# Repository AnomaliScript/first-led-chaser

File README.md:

# first-led-chaser
This project is meant to be an introduction to KiCad, as I have never fully, independently made a schematic before :(  Let's hope I can make this successfully!

## How to Use It
An LED Chaser is basically those glowing, flashy arcade signs that have a series of LEDs (not necessarily a series circuit, mind you) that light up in a particular order, whether it be every other LED that switches or the blinking LED follows a circular pattern.
It's purely for flashiness and style, and it looks cool!  For a project like mine, it can even show team spirit.  (Read more too see what team I'm making this LED Chaser for).

## Story and Why I Made This
First step of making the PCB is making the schematics.  In order to create a schematic, I used KiCad's schematic tool, and I placed a couple of components down, until I realized I needed to pull some components and their footprints (a footprint is what represents the component in the PCB editor) from a database called "Ultra Librarian" by Texas Instruments (they sponsor quite a lot of robotics teams).  After getting the needed schematics, I wired them together with the green copper lines, and learned how to use labels and global labels (global labels are the labels in the arrow shapes).

When switching over to the PCB editor for the second part of my project, I had to assign footprints to every one of the schematics: this is where Ultra Librarian helped me out in finding some footprints thatthe KiCad default library doesn't naturally have.

after hunting down all the footprints, I made the PCB board's shape.  This LED chaser I made is in the shape of my FRC Robotics Team's (1771) logo, and wiring it all together with the front and back coppers, with the help of vias, wasn't too daunting of a task the more I connected components.
It kinda felt like a game, connecting all of them together :)

Anyways, here's the final 3D result!

I'm debating on whether to make a case for it: I decided against it.

## BOM (my version)
0.01 uF Capacitors: [link](https://www.amazon.com/Cermant-Ceramic-Capacitor-Electronic-Components/dp/B09XV2CZJZ/ref=sr_1_3?sr=8-3)
1 uF Capacitors (and many more capacitors): [link](https://www.amazon.com/200PCS-Electrolytic-Capacitor-Kit-Electronics/dp/B0FH1R7N94/ref=sr_1_4?sr=8-4)
Connectors: [link](https://www.amazon.com/Glarks-Connector-Assortment-Stackable-Breakaway/dp/B07CWSXY7P)
4017BE: [link](https://www.amazon.com/Texas-Instruments-CD4017BE-Counter-Decoded/dp/B00GAGD10Y)
NE555N Clock: [link](https://www.amazon.com/ALLECIN-NE555-NE555P-Timer-NE555N/dp/B0CBKFMWDP)
T93YA: [link](https://www.digikey.com/en/products/detail/vishay-sfernice/T93YA103KT20/1587711)
In total, this project cost me about **$30** to make (yikes...)

## End Result
Fortunately, I got help from a friend when his dad agreed to lend me his solder and soldering iron.
When I initially soldered the PCB, [the blinking was really fast](https://drive.google.com/file/d/1CZGWTpNvm0oBers0KX6bNRDRQLqv2583/view?usp=sharing), even when I set the potentiometer to its "highest resistance" mode, which is stupposed to slow down the blinking rate.
After asking AI for help, I decided to replace the capacitor (which was originally 1uF) with a 10uF capacitor.

This solution worked, and after a few close burns, and the blinker works: a video of it blinking can be found [here](https://drive.google.com/file/d/13T7uWkx8QOqEzrhQr9J85-se3VObvKnz/view?usp=sharing) (the capacitor laying near the PCB was the 1uF capacitor that I removed).
Despite the blinker being a bit finicky at times, I learned a lot from this experience, and I'm still proud of the result.

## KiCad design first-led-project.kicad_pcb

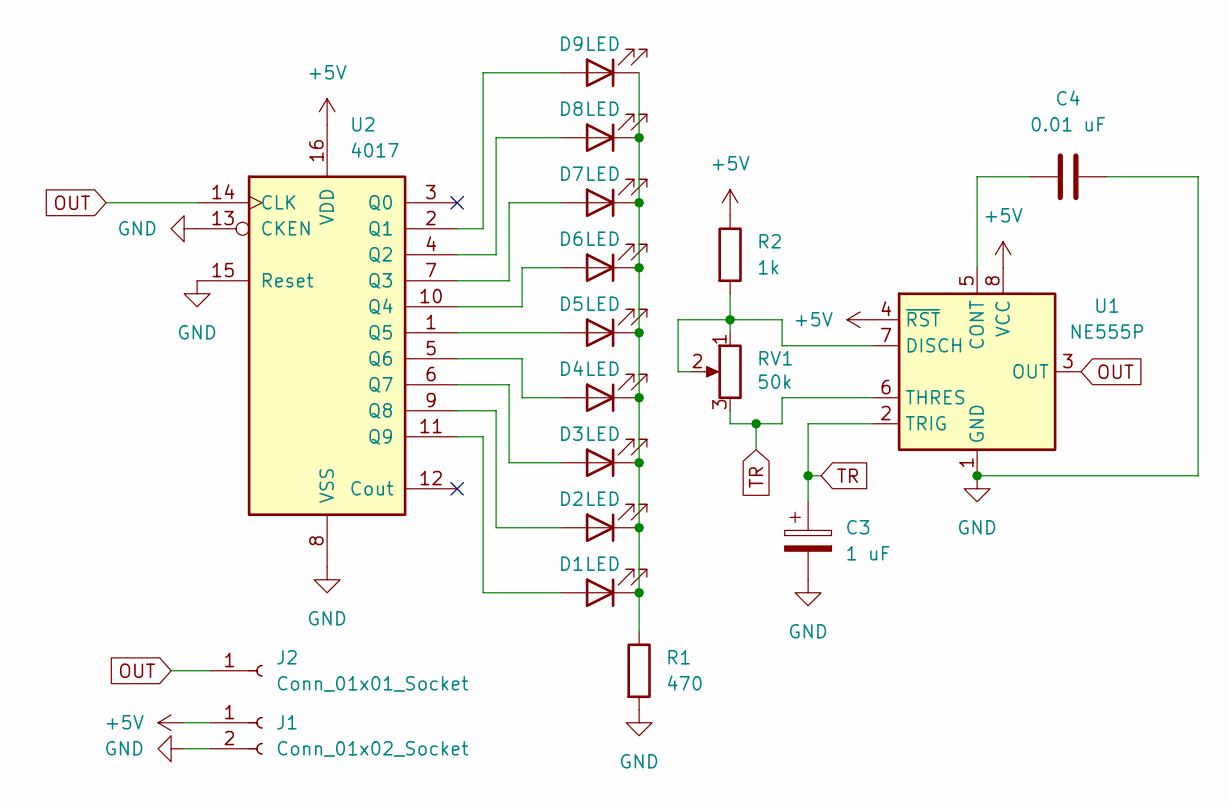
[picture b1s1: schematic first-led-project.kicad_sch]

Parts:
C3: 1 uF; CP_Radial_D5.0mm_P2.00mm
C4: 0.01 uF; C_Disc_D7.5mm_W2.5mm_P5.00mm
D1, D2, D3, D4, D5, D6, D7, D8, D9: LED; LED_D3.0mm
J1: Conn_01x02_Socket; PinHeader_1x02_P2.54mm_Vertical
J2: Conn_01x01_Socket; PinSocket_1x01_P2.54mm_Vertical
R1: 470; R_Axial_DIN0207_L6.3mm_D2.5mm_P7.62mm_Horizontal
R2: 1k; R_Axial_DIN0207_L6.3mm_D2.5mm_P7.62mm_Horizontal
RV1: 50k; Potentiometer_Vishay_T93YA_Vertical
U1: NE555P; DIP-8_W7.62mm
U2: 4017; N16

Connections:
+5V: J1.1, R2.1, U1.4 (~RST), U1.8 (VCC), U2.16 (VDD)
GND: C3.2, C4.2, J1.2, R1.2, U1.1 (GND), U2.8 (VSS), U2.13 (CKEN), U2.15 (Reset)
unnamed: D1.2 (A), U2.11 (Q9)
unnamed: D1.1 (K), D2.1 (K), D3.1 (K), D4.1 (K), D5.1 (K), D6.1 (K), D7.1 (K), D8.1 (K), D9.1 (K), R1.1
unnamed: D2.2 (A), U2.9 (Q8)
unnamed: D3.2 (A), U2.6 (Q7)
unnamed: D4.2 (A), U2.5 (Q6)
unnamed: D5.2 (A), U2.1 (Q5)
unnamed: D6.2 (A), U2.10 (Q4)
unnamed: D7.2 (A), U2.7 (Q3)
unnamed: D8.2 (A), U2.4 (Q2)
unnamed: D9.2 (A), U2.2 (Q1)
unnamed: C4.1, U1.5 (CONT)
unnamed: R2.2, RV1.1, RV1.2, U1.7 (DISCH)
OUT: J2.1 (Pin_1_1), U1.3 (OUT), U2.14 (CLK)
TR: C3.1, RV1.3, U1.2 (TRIG), U1.6 (THRES)

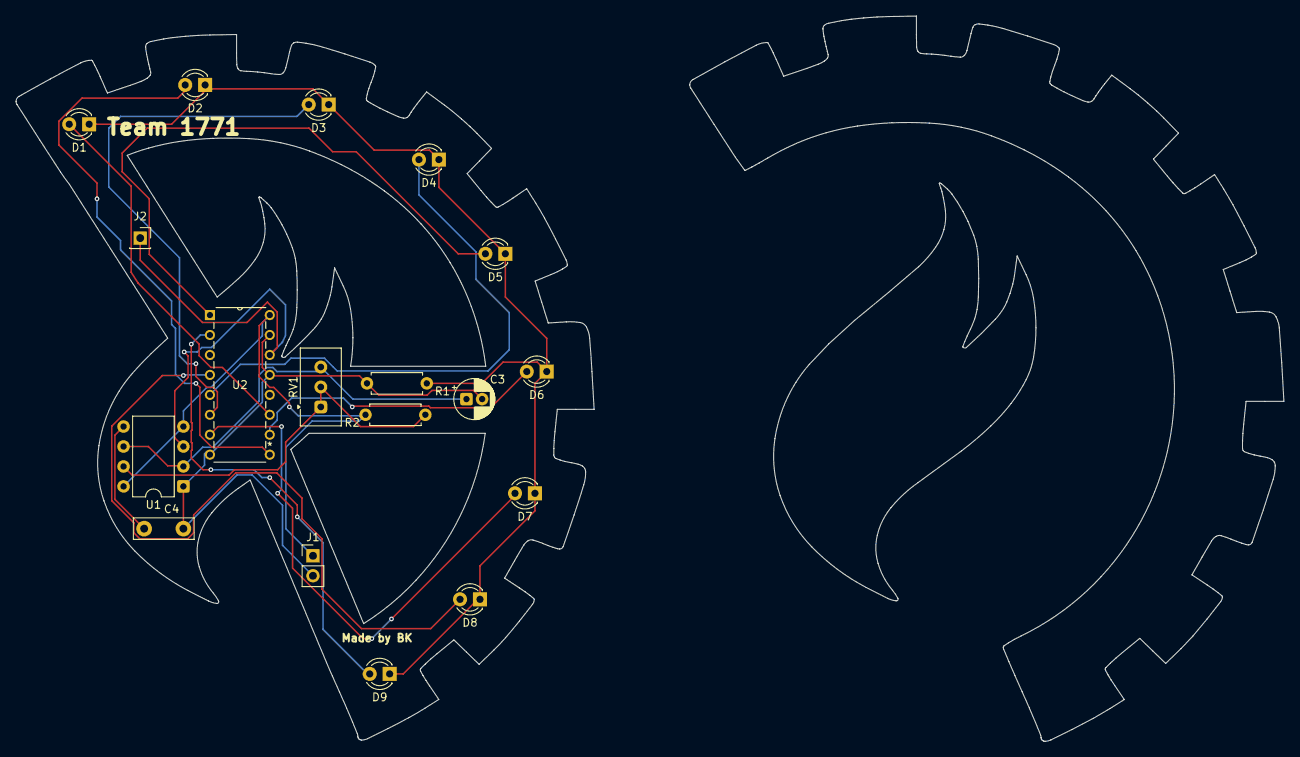
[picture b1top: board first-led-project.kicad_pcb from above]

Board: 2 copper layers, 73.6 x 89.8 mm, 18 parts (0 on the bottom side), 16 nets.

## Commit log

2026-04-24 Add Screenshot of 3D View
2026-04-24 Adding Gerbers
2026-04-24 Update README with project details and images
    Expanded project description with detailed steps and images.
2026-04-24 Adding BOM
2026-04-24 Update README with project details and usage
    Added sections on usage, story, and end result of the LED Chaser project.
2026-05-21 Revise case decision and add BOM section
    Updated the decision on making a case and added a BOM section with links to components.
2026-06-22 Update README with project cost and soldering details
    Added project cost and detailed soldering experience.
